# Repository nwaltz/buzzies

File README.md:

# buzzies
bilateral stimulation tappers for use as a EMDR therapy device through Engineers Without Borders OSU

top level models:

pods: final pod assm.SLDASM

pcb case: pcb assm no snaps.SLDASM

## Production

There are several ways to manufacture the mechanical components needed to house the electrical components for the buzzies.  While the original design concept was produced using a resin SLA printer (Prusa SLIS and Formlabs 3+), components were also designed for injection molding and filament 3D printing.  Each component will have subfolders containing the CAD models, and the subsections below will describe how to manufacture these components.

### Resin SLA Printing

The motivation behind using an SLA printer was to retain the smooth and polished surface finish of an injection molded part while allowing for overhangs and otherwise difficult to manufacture features.  There are four unique parts to manufacture in this design: 4 identical pod halves, a pcb base case, a pcb back cover, and a battery back cover.  

The pod halves are rotationally symmetric about the centerline and will hold a small piezo vibration motor in the center cavity.  Since such motors will generally have small, fragile wires, we recommmend soldering larger (e.g. 16 AWG) wires to the ends of the motor wires.  There is space to house the solder connection within the pods to maintain the strength of the connection. 

Once the motors are soldered and housed within the pods, the pod halves need to be fastened together.  The pod halves will self-align when placed together, and will be fastened with two dowel pins.  There should be two small holes on the side of the pod that the wires exit from.  Insert the dowel pins into these holes to fasten the pods together.  The end of the pin should be flush with the face of the pod.  If the pins seem to be sticking, you may need to lightly tap them with a hammer.

### Injection Molding

### Filament Printing

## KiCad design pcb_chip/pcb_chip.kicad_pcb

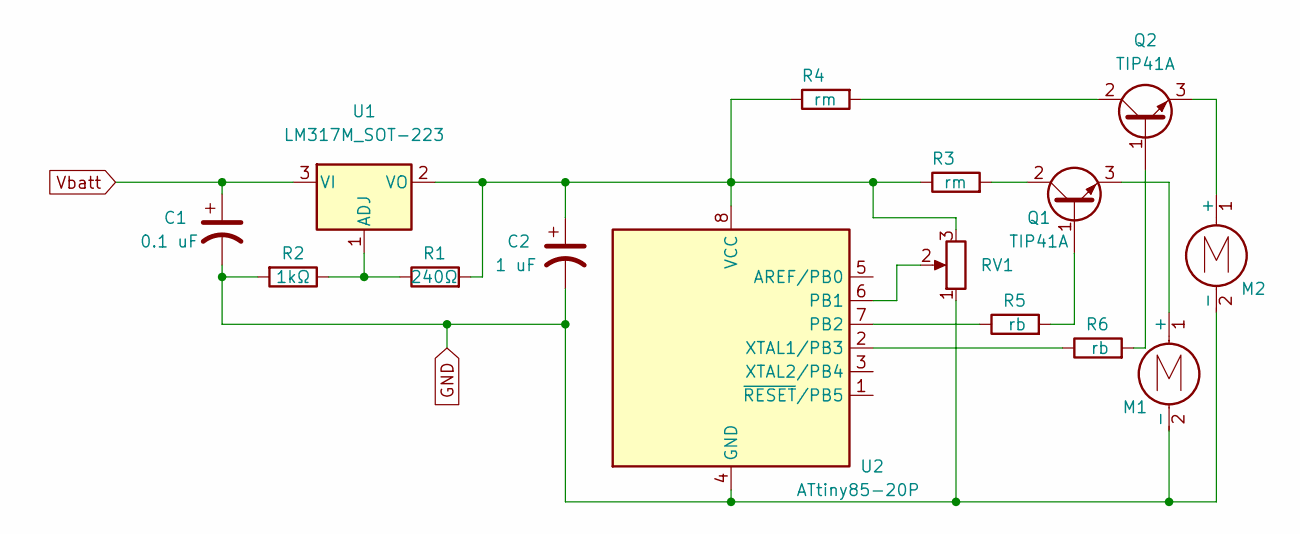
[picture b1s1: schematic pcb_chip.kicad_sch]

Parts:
C1: 0.1 uF; CP_Elec_4x5.4
C2: 1 uF; CP_Elec_4x5.4
M1, M2: vib_mot; PinHeader_1x02_P2.54mm_Vertical
Q1, Q2: TIP41A; SOT-23
R1: 240Ω; R_1206_3216Metric
R2: 1kΩ; R_1206_3216Metric
R3, R4: rm; R_1206_3216Metric
R5, R6: rb; R_1206_3216Metric
RV1: R_Potentiometer
U1: LM317M_SOT-223; SOT-223-3_TabPin2
U2: ATtiny85-20P; DIP-8_W7.62mm

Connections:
GND: C1.2, C2.2, M1.2 (-), M2.2 (-), R2.2, RV1.1, U2.4 (GND); also elsewhere on the board
unnamed: C2.1, R1.2, R3.1, R4.1, RV1.3, U1.2 (VO), U2.8 (VCC)
unnamed: M1.1 (+), Q1.3 (E)
unnamed: M2.1 (+), Q2.3 (E)
unnamed: R1.1, R2.1, U1.1 (ADJ)
unnamed: Q1.2 (C), R3.2
unnamed: Q2.2 (C), R4.2
unnamed: R5.1, U2.7 (PB2)
unnamed: Q1.1 (B), R5.2
unnamed: R6.1, U2.2 (XTAL1/PB3)
unnamed: Q2.1 (B), R6.2
unnamed: RV1.2, U2.6 (PB1)
Vbatt: C1.1, U1.3 (VI); also elsewhere on the board

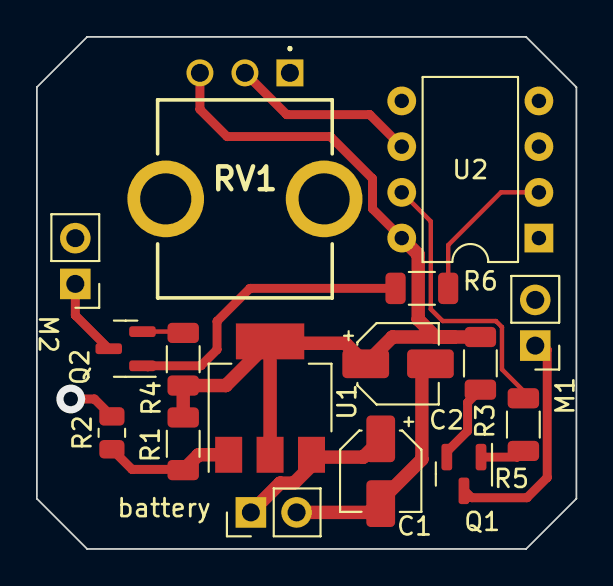
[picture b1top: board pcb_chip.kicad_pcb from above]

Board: 2 copper layers, 30.0 x 28.4 mm, 16 parts (0 on the bottom side), 13 nets.

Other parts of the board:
battery: vib_mot; PinHeader_1x02_P2.54mm_Vertical

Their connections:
GND: battery.2 (-); also elsewhere on the board
Vbatt: battery.1 (+); also elsewhere on the board

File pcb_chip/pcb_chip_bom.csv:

Id,Designator,Footprint,Quantity,Comment,JLCPCB Part #?optional?,Column1
1,U2,DIP-8_W7.62mm,1,IC-8P,C5289485,
2,"R6,R5",R_1206_3216Metric,2,rb,C245596,
3,"Q1,Q2",SOT-23,2,TIP41A,C141788,
4,"R3,R4",R_1206_3216Metric,2,rm,C237774,
5,C2,CASE-A-3216,1,1 uF,C128315,
6,R2,805,1,1k?,C5139712,
7,R1,R_1206_3216Metric,1,240?,C3017200,
10,C1,"SMD,1.6x3.2mm",1,0.1 uF,C2976899,
11,U1,SOT-223-3_TabPin2,1,LM317M_SOT-223,C840113,
12,RV1,,1,pot,C470307,

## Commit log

2023-02-20 updated dependencies
2023-02-20 pod template
2023-02-21 test
2023-03-07 Added a circular snap fit option.
2024-02-27 added pcb files
2024-08-30 added pod cad file, it does have snaps ignore the name
2024-09-09 add chip code
2024-09-29 Rename pod no snaps.SLDPRT to pod with snaps.SLDPRT
